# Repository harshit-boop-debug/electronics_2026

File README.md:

## Project Structure

This repository contains 2 firmware projects, each for a different operational mode of the Rover. Only **one folder is flashed to Teensy at a time** — either autonomous or manual.

A shared `Assets/` folder holds all hardware-related documents (PCB files, datasheets, etc.) used across both modes.

```
Embedded_UGVC/
│
├── Assets/                    # Shared hardware resources
│   ├── PCB Files/             # KiCad schematic and layout files
│   └── Datasheet/             # IC, MCU, and component datasheets
│
├── Autonomous Mode/           # Firmware for autonomous navigation tasks
│   ├── platformio.ini
│   ├── src/                   
│   ├── include/               
│   ├── lib/                  
│   └── test/                  
│
├── Manual Mode/               # Firmware for manual / RC-controlled tasks
│   ├── platformio.ini
│   ├── src/                   
│   ├── include/               
│   ├── lib/                   
│   └── test/                  
│
└── README.md
```

## `src/` — Source Files

One `.cpp` file per subsystem. **Do not put everything in `main.cpp`.**

- `main.cpp` — Only `setup()` and `loop()`. Calls functions from other modules.
- Add a new `.cpp` for every new subsystem (e.g. `motor_control.cpp`, `encoder.cpp`, `jetson_comm.cpp`, `pid.cpp`, `imu.cpp`).

---

## `include/` — Header Files

Every `.cpp` in `src/` gets a matching `.h` here. Use `#pragma once` at the top of every header.

- **All pin numbers, baud rates, and tuning constants go in `config.h`** — never hardcode them inside `.cpp` files.

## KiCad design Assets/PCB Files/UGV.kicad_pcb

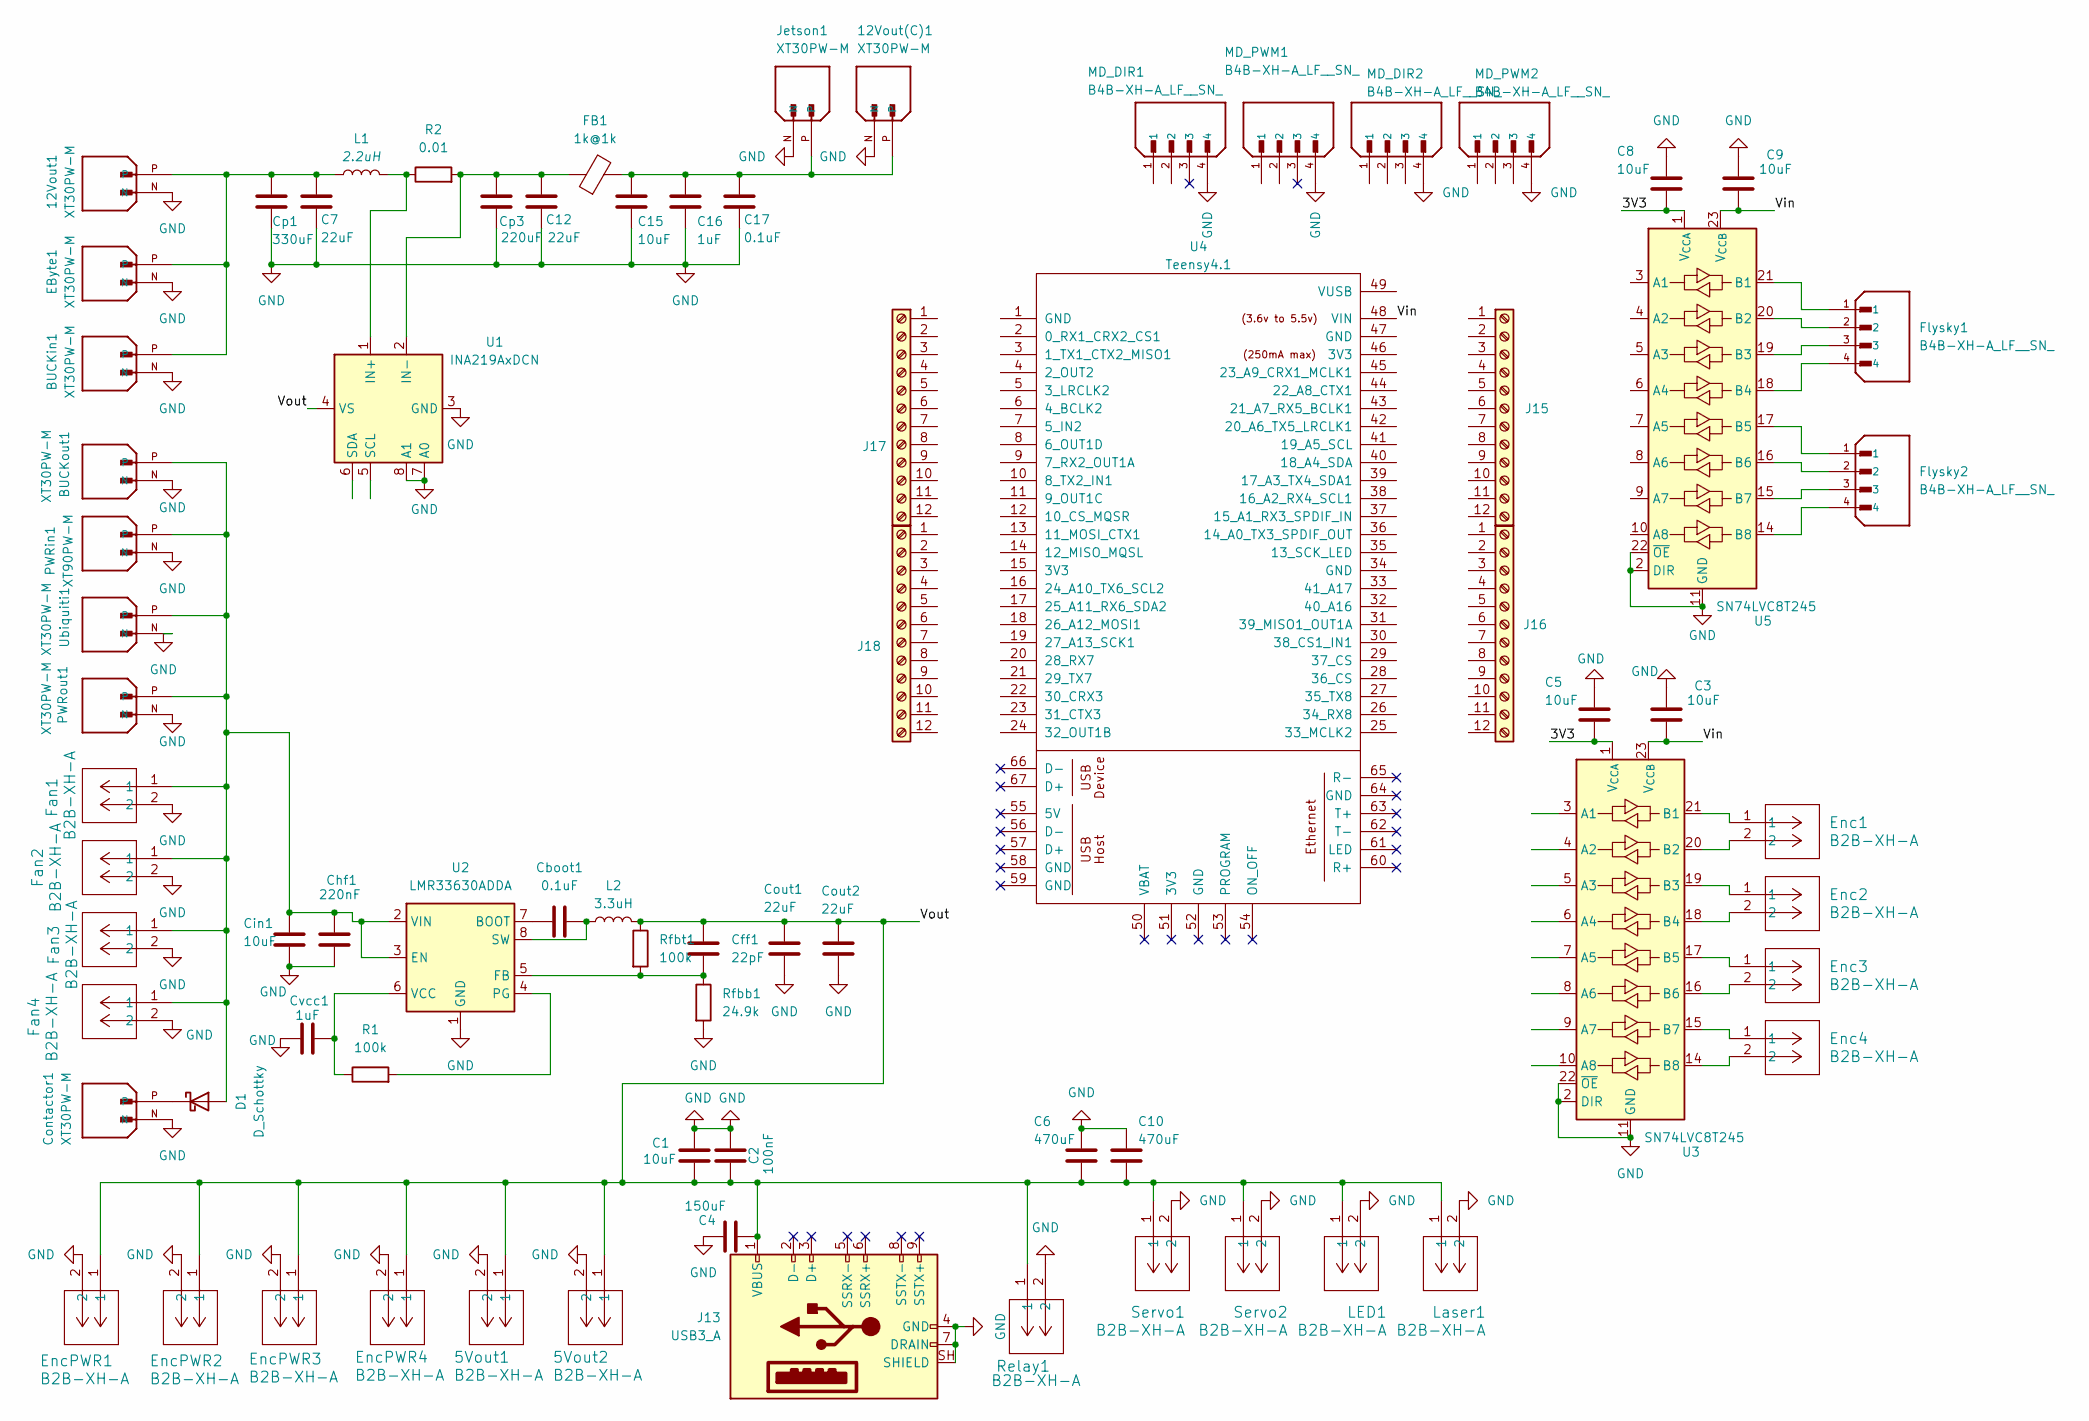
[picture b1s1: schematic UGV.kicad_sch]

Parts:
5Vout1, 5Vout2: B2B-XH-A; JST_XH_B2B-XH-A_1x02_P2.50mm_Vertical
12Vout1, 12Vout(C)1: XT30PW-M; AMASS_XT30PW-M; PARTREV 1.2
BUCKin1: XT30PW-M; AMASS_XT30PW-M; PARTREV 1.2
BUCKout1: XT30PW-M; AMASS_XT30PW-M; PARTREV 1.2
C1, C3, C5, C8, C9, C15: 10uF; C_1210_3225Metric
C2: 100nF; C_0603_1608Metric
C4: 150uF; CP_Elec_8x10.5
C6, C10: 470uF; CP_Radial_D8.0mm_P3.50mm
C7, C12: 22uF; C_1210_3225Metric
C16: 1uF; C_0603_1608Metric
C17: 0.1uF; C_0603_1608Metric
Cboot1: 0.1uF; C_0603_1608Metric
Cff1: 22pF; C_0603_1608Metric
Chf1: 220nF; C_1206_3216Metric
Cin1: 10uF; C_1210_3225Metric
Contactor1: XT30PW-M; AMASS_XT30PW-M; PARTREV 1.2
Cout1, Cout2: 22uF; C_0603_1608Metric_Pad1.08x0.95mm_HandSolder
Cp1: 330uF; CP_Radial_D10.0mm_P5.00mm
Cp3: 220uF; CP_Elec_10x10
Cvcc1: 1uF; C_0603_1608Metric
D1: D_Schottky; D_SMC_Handsoldering
EByte1: XT30PW-M; AMASS_XT30PW-M; PARTREV 1.2
Enc1, Enc2, Enc3, Enc4: B2B-XH-A; JST_XH_B2B-XH-A_1x02_P2.50mm_Vertical
EncPWR1, EncPWR2, EncPWR3, EncPWR4: B2B-XH-A; JST_XH_B2B-XH-A_1x02_P2.50mm_Vertical
FB1: 1k@1k; BEADC2012X105N
Fan1, Fan2, Fan3, Fan4: B2B-XH-A; JST_XH_B2B-XH-A_1x02_P2.50mm_Vertical
Flysky1, Flysky2: B4B-XH-A_LF__SN_; JST_B4B-XH-A_LF__SN_; PARTREV 7/4/21
J13: USB3_A; USB-3.0-TH_U233-091N-4BLPC17-11
J15, J16, J17, J18: Screw_Terminal_01x12; TerminalBlock_Phoenix_MPT-0,5-12-2.54_1x12_P2.54mm_Horizont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
Jetson1: XT30PW-M; AMASS_XT30PW-M; PARTREV 1.2
L1: 2.2uH; L_Vishay_IHLP-2525
L2: 3.3uH; L_Vishay_IHLP-2525
LED1: B2B-XH-A; JST_XH_B2B-XH-A_1x02_P2.50mm_Vertical
Laser1: B2B-XH-A; JST_XH_B2B-XH-A_1x02_P2.50mm_Vertical
MD_DIR1, MD_DIR2: B4B-XH-A_LF__SN_; JST_B4B-XH-A_LF__SN_; PARTREV 7/4/21
MD_PWM1, MD_PWM2: B4B-XH-A_LF__SN_; JST_B4B-XH-A_LF__SN_; PARTREV 7/4/21
PWRin1: XT90PW-M; AMASS_XT90PW-M; PARTREV 1.2
PWRout1: XT30PW-M; AMASS_XT30PW-M; PARTREV 1.2
R1: 100k; R_0402_1005Metric
R2: 0.01; R_0402_1005Metric
Relay1: B2B-XH-A; JST_XH_B2B-XH-A_1x02_P2.50mm_Vertical
Rfbb1: 24.9k; R_0402_1005Metric
Rfbt1: 100k; R_0402_1005Metric
Servo1, Servo2: B2B-XH-A; JST_XH_B2B-XH-A_1x02_P2.50mm_Vertical
U1: INA219AxDCN; SOT-23-8
U2: LMR33630ADDA; CONV_LMR33620BRNXT
U3, U5: SN74LVC8T245; SOIC127P1030X265-24N
U4: Teensy4.1; Teensy41
Ubiquiti1: XT30PW-M; AMASS_XT30PW-M; PARTREV 1.2

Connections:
/3V3: C5.2, C8.2, U3.1 (V_{CCA}), U5.1 (V_{CCA})
/Vin: C3.2, C9.2, U3.23 (V_{CCB}), U3.24 (V_{CCB}), U4.48 (VIN_48), U5.23 (V_{CCB}), U5.24 (V_{CCB})
/Vout: 5Vout1.1, 5Vout2.1, C1.2, C2.1, C4.1, C6.2, C10.2, Cff1.1, Cout1.1, Cout2.1, EncPWR1.1, EncPWR2.1, EncPWR3.1, EncPWR4.1, J13.1 (VBUS), L2.2, LED1.1, Laser1.1, Relay1.1, Rfbt1.1, Servo1.1, Servo2.1, U1.4 (VS)
GND: 5Vout1.2, 5Vout2.2, 12Vout1.N, 12Vout(C)1.N, BUCKin1.N, BUCKout1.N, C1.1, C2.2, C3.1, C4.2, C5.1, C6.1, C7.2, C8.1, C9.1, C10.1, C12.2, C15.2, C16.2, C17.2, Chf1.2, Cin1.2, Contactor1.N, Cout1.2, Cout2.2, Cp1.2, Cp3.2, Cvcc1.2, EByte1.N, EncPWR1.2, EncPWR2.2, EncPWR3.2, EncPWR4.2, Fan1.2, Fan2.2, Fan3.2, Fan4.2, J13.4 (GND), J13.7 (DRAIN), J13.SH (SHIELD), Jetson1.N, LED1.2, Laser1.2, MD_DIR1.4 (4_4), MD_DIR2.4 (4_4), MD_PWM1.4 (4_4), MD_PWM2.4 (4_4), PWRin1.N, PWRout1.N, Relay1.2, Rfbb1.2, Servo1.2, Servo2.2, U1.3 (GND), U1.7 (A0), U1.8 (A1), U2.1 (GND), U2.9 (GND), U3.2 (DIR), U3.11 (GND), U3.12 (GND), U3.13 (GND), U3.22 (~OE), U5.2 (DIR), U5.11 (GND), U5.12 (GND), U5.13 (GND), U5.22 (~OE), Ubiquiti1.N
unnamed: 12Vout1.P, BUCKin1.P, C7.1, Cp1.1, EByte1.P, L1.1
unnamed: 12Vout(C)1.P, C15.1, C16.1, C17.1, FB1.2, Jetson1.P
unnamed: BUCKout1.P, Chf1.1, Cin1.1, D1.2 (A), Fan1.1, Fan2.1, Fan3.1, Fan4.1, PWRin1.P, PWRout1.P, U2.2 (VIN), U2.3 (EN), Ubiquiti1.P
unnamed: Contactor1.P, D1.1 (K)
unnamed: L1.2, R2.1, U1.1 (IN+)
unnamed: C12.1, Cp3.1, FB1.1, R2.2, U1.2 (IN-)
unnamed: Cboot1.1, U2.7 (BOOT)
unnamed: Cff1.2, Rfbb1.1, Rfbt1.2, U2.5 (FB)
unnamed: R1.2, U2.4 (PG)
unnamed: Cboot1.2, L2.1, U2.8 (SW)
unnamed: Cvcc1.1, R1.1, U2.6 (VCC)
unnamed: Enc1.1, U3.21 (B1)
unnamed: Enc1.2, U3.20 (B2)
unnamed: Enc2.1, U3.19 (B3)
unnamed: Enc2.2, U3.18 (B4)
unnamed: Enc3.1, U3.17 (B5)
unnamed: Enc3.2, U3.16 (B6)
unnamed: Enc4.1, U3.15 (B7)
unnamed: Enc4.2, U3.14 (B8)
unnamed: Flysky1.1, U5.21 (B1)
unnamed: Flysky1.2, U5.20 (B2)
unnamed: Flysky1.3, U5.19 (B3)
unnamed: Flysky1.4, U5.18 (B4)
unnamed: Flysky2.1, U5.17 (B5)
unnamed: Flysky2.2, U5.16 (B6)
unnamed: Flysky2.3, U5.15 (B7)
unnamed: Flysky2.4, U5.14 (B8)

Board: 2 copper layers, 76 parts (0 on the bottom side), 31 nets, no tracks yet.

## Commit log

2026-04-04 Initial project structure
2026-04-04 Added Datasheets
2026-04-04 Footprints added
2026-04-08 Added Files to Include
2026-04-09 Fixed structure
2026-04-14 Update README to include Estop system information
    Added Estop section to README with details on Wireless Emergency Stop system.
2026-04-14 Estop
2026-04-18 Update README with MAC_ID flashing instructions
2026-04-25 PCB updated
